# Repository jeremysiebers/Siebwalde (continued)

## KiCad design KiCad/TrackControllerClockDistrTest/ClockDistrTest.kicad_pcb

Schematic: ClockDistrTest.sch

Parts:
C1, C3: 12p; C_1206_3216Metric
C2, C7, C9, C11, C13, C15, C19, C20, C23, C24, C25: 0.1u; C_1206_3216Metric
C4, C6, C8, C12, C14, C16, C17, C18, C21, C22, C26: 22u; C_1206_3216Metric
C5, C10: 10pF; C_1206_3216Metric
D1: DIODE; D_DO-15_P10.16mm_Horizontal
D2: LED; LED_D5.0mm
J1, J2, J3, J4, J8, J9, J10, J11, J12, J13, J14, J15, J16, J17, J18, J19, J20, J21, J22: Conn_01x02_Male; PinHeader_1x02_P2.54mm_Vertical
R1, R2, R5, R7, R8, R9, R13, R14, R18: 10E; R_1206_3216Metric
R3: 1M; R_1206_3216Metric
R4: 270; R_1206_3216Metric
R6: 300; R_1206_3216Metric
R10, R12, R15, R17: 1K; R_1206_3216Metric
R11, R16: 120E; R_1206_3216Metric
U1: 4049; DIP-16_W7.62mm
U2: NB3N511; SOIC-8_3.9x4.9mm_P1.27mm
U3: LM7805_TO220; TO-220-3_Horizontal_TabDown
U4, U9: MAX14783E; SOIC-8_3.9x4.9mm_P1.27mm
U5, U6, U7, U8: MAX3284E; SOT-23-6
X1: SG-531; Oscillator_SeikoEpson_SG-8002DC
Y1, Y2: Crystal; Crystal_HC49-U_Vertical

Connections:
+5V: C13.1, C14.1, R1.1, R2.1, R5.2, R6.1, R7.2, R8.1, R9.1, R10.2, R13.1, R14.1, R15.2, R18.2, U3.3 (VO)
/RS422-B: J8.2, R10.1, R11.2, U4.7 (B)
A1: J9.1, J10.1, U5.6
A2: J11.1, J12.1, U6.6
A3: J13.1, J16.1, U7.6
A4: J17.1, J18.1, U8.6
B1: J9.2, J10.2, U5.4
B2: J11.2, J12.2, U6.4
B3: J13.2, J16.2, U7.4
B4: J17.2, J18.2, U8.4
GND: C1.2, C2.2, C3.2, C4.2, C5.2, C6.2, C7.2, C8.2, C9.2, C10.2, C11.2, C12.2, C13.2, C14.2, C15.2, C16.2, C17.2, C18.2, C19.2, C20.2, C21.2, C22.2, C23.2, C24.2, C25.2, C26.2, D2.1, J1.2, J14.1, J15.1, J20.1, J21.1, J22.1, R12.1, R17.1, U1.8 (VSS), U2.3 (GND), U3.2 (GND), U4.5 (GND), U5.2, U6.2, U7.2, U8.2, U9.2 (~RE), U9.3 (DE), U9.5 (GND), X1.4 (GND)
unnamed: C1.1, U2.1 (X1/CLK), Y1.1
unnamed: C2.1, C4.1, R1.2, U1.1 (VCC)
unnamed: C3.1, U2.8 (X2), Y1.2
unnamed: C5.1, R3.2, U1.3, Y2.2
unnamed: C6.1, C7.1, R2.2, X1.1 (OE), X1.8 (Vcc)
unnamed: C8.1, C9.1, D1.2, U3.1 (VI)
unnamed: C10.1, R4.1, Y2.1
unnamed: C11.1, C12.1, R5.1, U2.2 (Vdd), U2.7 (OE)
unnamed: C15.1, C16.1, R7.1, U4.2 (~RE), U4.3 (DE), U4.8 (VCC)
unnamed: C17.1, C19.1, R8.2, U5.1, U5.5
unnamed: C18.1, C20.1, R9.2, U6.1, U6.5
unnamed: C21.1, C23.1, R13.2, U7.1, U7.5
unnamed: C22.1, C24.1, R14.2, U8.1, U8.5
unnamed: C25.1, C26.1, R18.1, U9.8 (VCC)
unnamed: D1.1, J1.1
unnamed: D2.2, R6.2
unnamed: J2.1, J3.1, J4.1, U4.4 (DI)
unnamed: J2.2, X1.5 (OUT)
unnamed: J3.2, U1.15
unnamed: J4.2, U2.5 (CLKOUT)
unnamed: J8.1, R11.1, R12.2, U4.6 (A)
unnamed: J14.2, U6.3
unnamed: J15.2, U5.3
unnamed: J19.1, R16.1, R17.2, U9.6 (A)
unnamed: J19.2, R15.1, R16.2, U9.7 (B)
unnamed: J20.2, U7.3
unnamed: J21.2, U8.3
unnamed: J22.2, U9.1 (RO)
unnamed: R3.1, R4.2, U1.2, U1.5
unnamed: U1.4, U1.7, U1.9, U1.11, U1.14

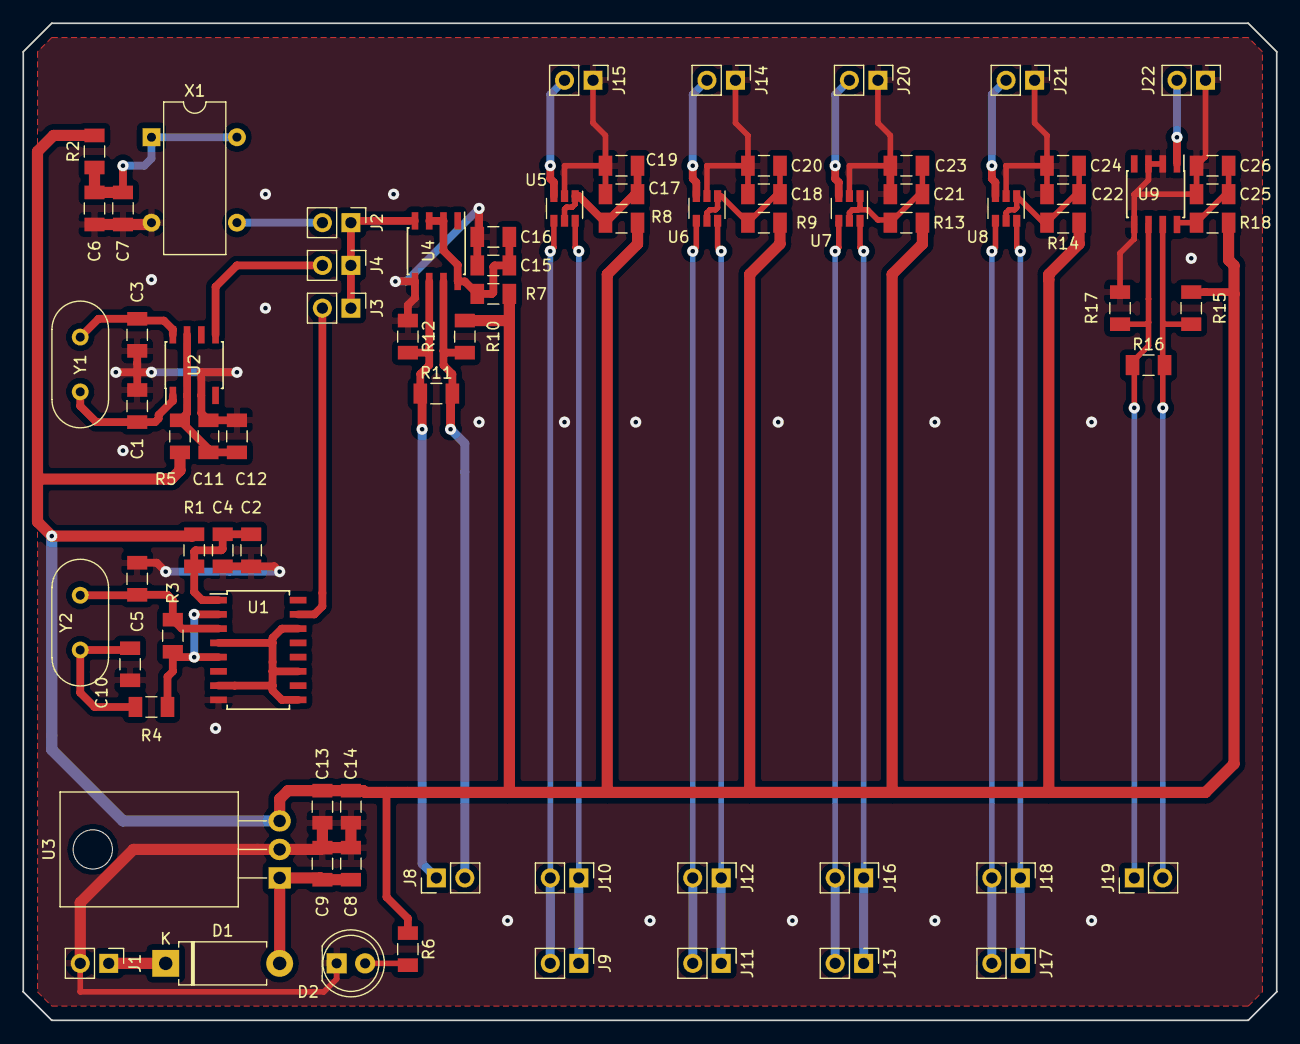
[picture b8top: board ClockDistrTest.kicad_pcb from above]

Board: 2 copper layers, 111.8 x 88.9 mm, 77 parts (0 on the bottom side), 41 nets.
